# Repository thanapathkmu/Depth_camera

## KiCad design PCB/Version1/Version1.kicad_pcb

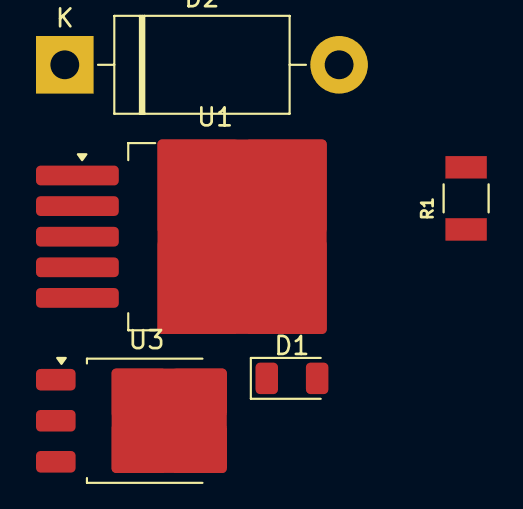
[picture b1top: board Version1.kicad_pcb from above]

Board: 2 copper layers, 5 parts (0 on the bottom side), 4 nets, no tracks yet.

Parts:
D1: IR26-21C; LED_1206_3216Metric
D2: 1N5822; D_DO-201AD_P15.24mm_Horizontal
R1: 2.2 k; RES_ERJU14J1R5U
U1: LM2576HVS-3.3; TO-263-5_TabPin3
U3: AMS1117CD-2.5V; TO-252-3_TabPin2

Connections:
12 V: R1.1, U1.1 (VIN)
GND: D1.1 (K), D2.2 (A), U1.3 (GND), U1.5 (~ON/OFF), U3.1 (GND)
unnamed: D1.2 (A), R1.2
unnamed: D2.1 (K), U1.2 (OUT)

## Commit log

2024-05-28 Code and Picture
2024-05-28 PCB and CAD design
2024-05-29 Update image path
2024-06-14 Final
